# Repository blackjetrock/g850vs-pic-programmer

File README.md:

# g850vs-pic-programmer
PIC programmer for G850VS

These are the files for a PIC programmer for a Sharp PC-G850V or PC-G850VS pocket computer.
The PIC programmer is from a ciruit i found on the internet. I have had permission to use the circuit
so that people can use it to program PICs. 

The PIC prototype PCB is based on the test circuit in the PC-G850 manual, except that, for some reaosn,
I changed the GPIO line that the LED is driven from. The example program given in the manual will have to 
be adjusted appropriately.

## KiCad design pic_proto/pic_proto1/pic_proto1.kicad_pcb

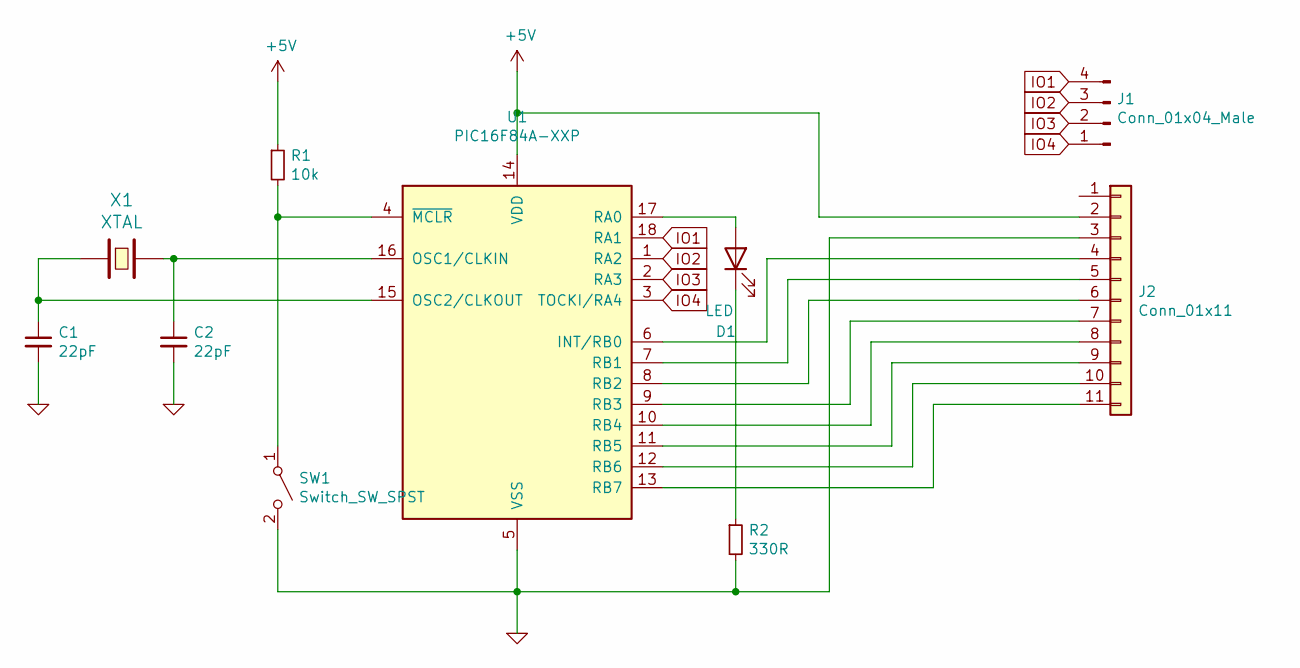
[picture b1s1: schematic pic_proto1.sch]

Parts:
C1, C2: 22pF; C_Disc_D7.5mm_W5.0mm_P5.00mm
D1: LED; LED_D5.0mm
J1: Conn_01x04_Male; Molex_KK-254_AE-6410-04A_1x04_P2.54mm_Vertical
J2: Conn_01x11; Molex_KK-254_AE-6410-11A_1x11_P2.54mm_Vertical
R1: 10k; R_Axial_DIN0204_L3.6mm_D1.6mm_P7.62mm_Horizontal
R2: 330R; R_Axial_DIN0204_L3.6mm_D1.6mm_P7.62mm_Horizontal
SW1: Switch_SW_SPST; SW_PUSH-12mm
U1: PIC16F84A-XXP; DIP-18_W7.62mm
X1: XTAL; Crystal_HC49-4H_Vertical

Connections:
+5V: J2.2, R1.1, U1.14 (VDD)
GND: C1.2, C2.2, J2.3, R2.2, SW1.2 (B), U1.5 (VSS)
IO1: J1.4, U1.18 (RA1)
IO2: J1.3, U1.1 (RA2)
IO3: J1.2, U1.2 (RA3)
IO4: J1.1, U1.3 (TOCKI/RA4)
unnamed: C1.1, U1.15 (OSC2/CLKOUT), X1.1
unnamed: C2.1, U1.16 (OSC1/CLKIN), X1.2
unnamed: D1.1 (K), R2.1
unnamed: D1.2 (A), U1.17 (RA0)
unnamed: J2.4, U1.6 (INT/RB0)
unnamed: J2.5, U1.7 (RB1)
unnamed: J2.6, U1.8 (RB2)
unnamed: J2.7, U1.9 (RB3)
unnamed: J2.8, U1.10 (RB4)
unnamed: J2.9, U1.11 (RB5)
unnamed: J2.10, U1.12 (RB6)
unnamed: J2.11, U1.13 (RB7)
unnamed: R1.2, SW1.1 (A), U1.4 (~MCLR~)

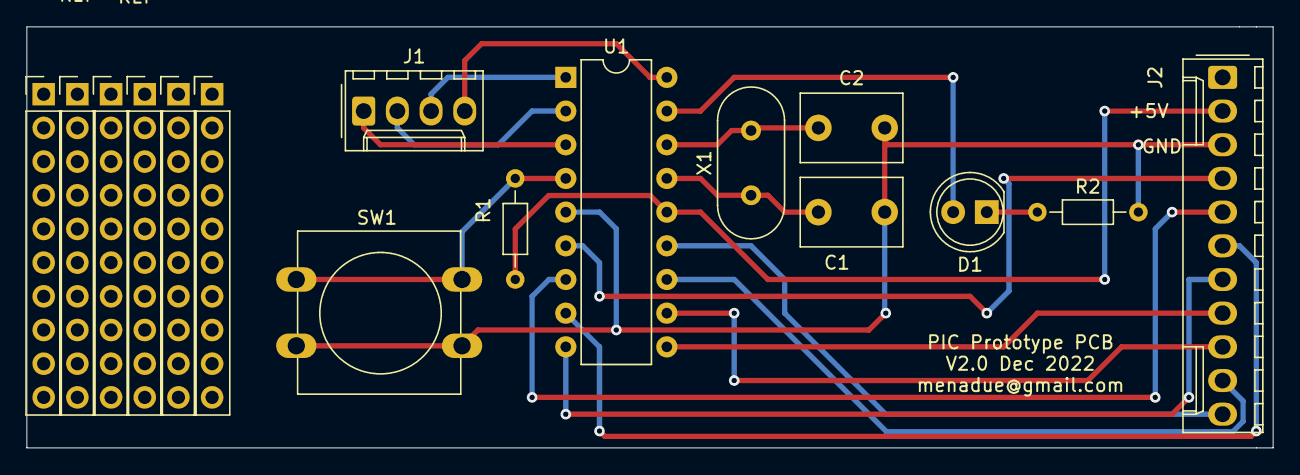
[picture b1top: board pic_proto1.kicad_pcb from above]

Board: 2 copper layers, 94.0 x 31.8 mm, 10 parts (0 on the bottom side), 19 nets.

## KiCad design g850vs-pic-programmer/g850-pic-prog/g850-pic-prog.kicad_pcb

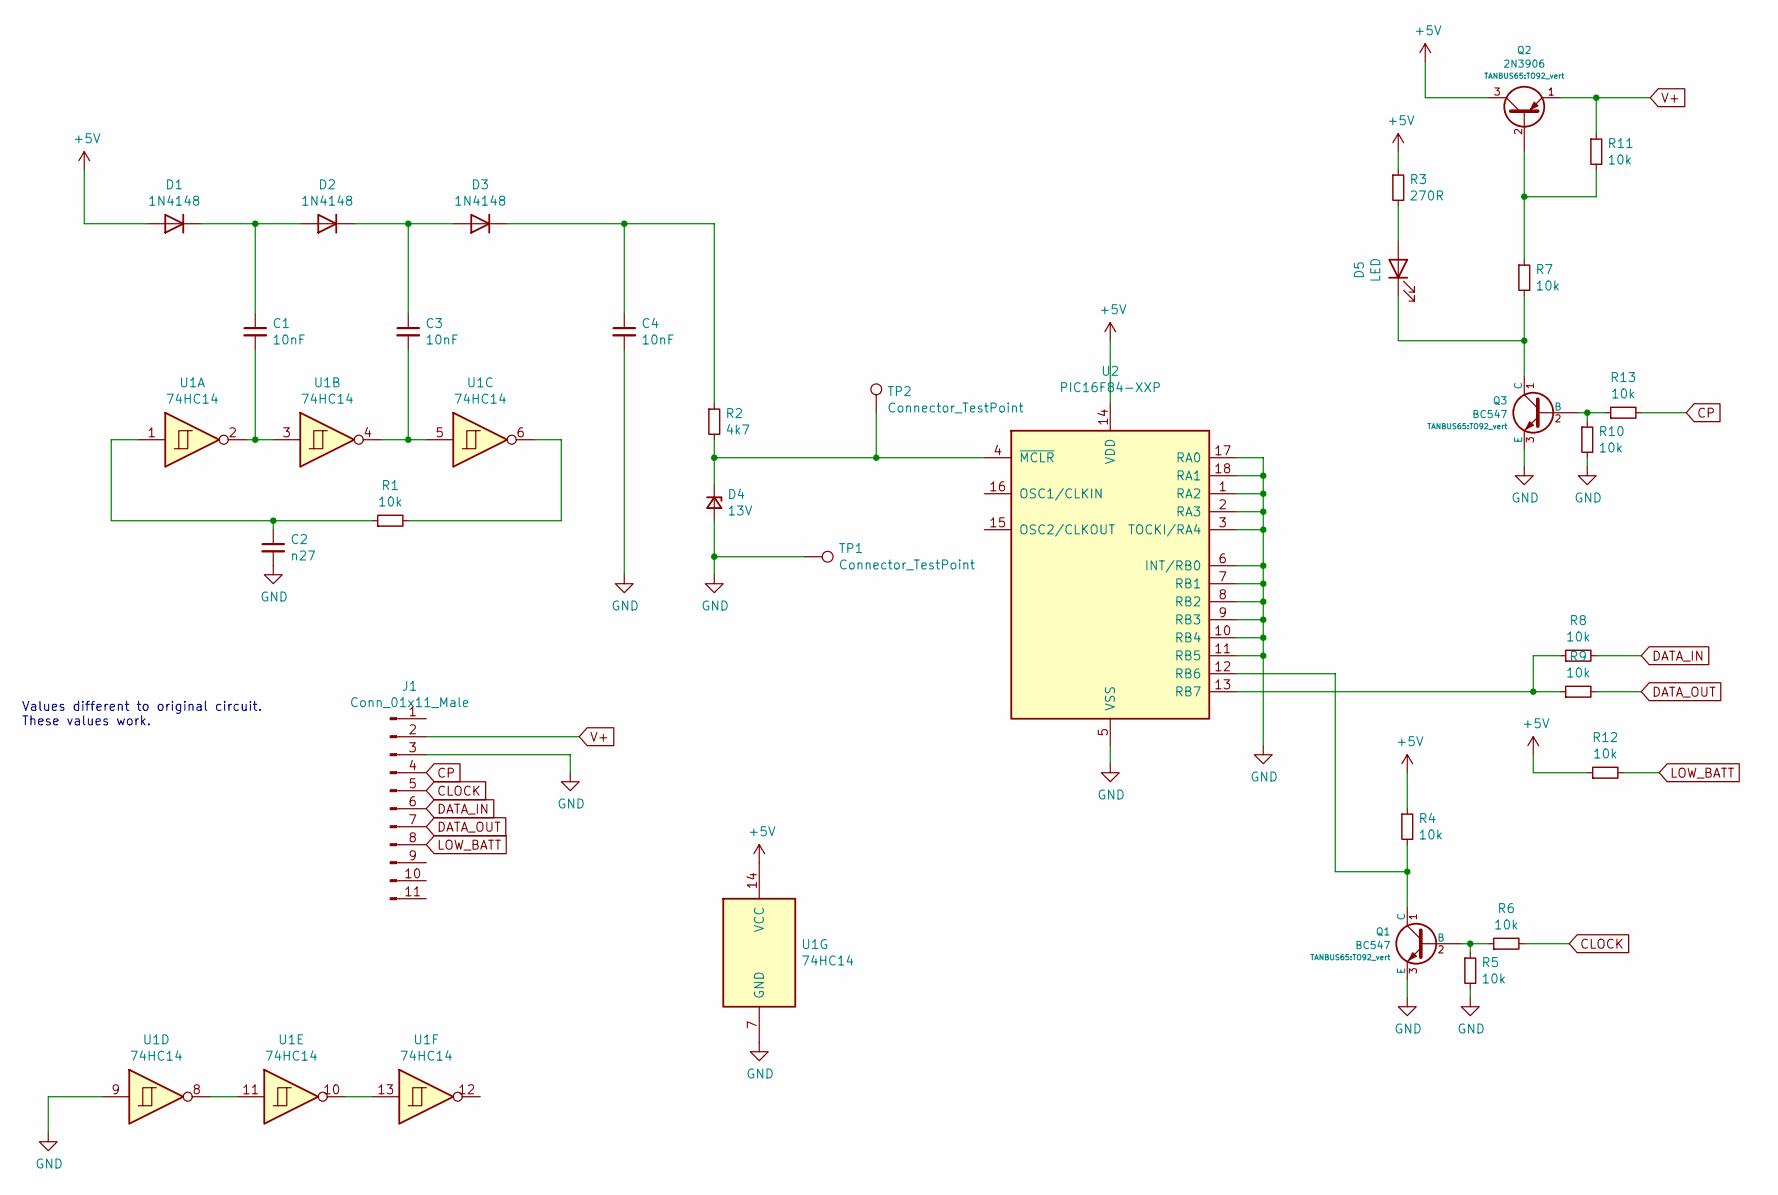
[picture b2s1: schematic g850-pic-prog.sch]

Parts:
C1, C3, C4: 10nF; C_Axial_L5.1mm_D3.1mm_P7.50mm_Horizontal
C2: n27; C_Axial_L5.1mm_D3.1mm_P7.50mm_Horizontal
D1, D2, D3: 1N4148; D_DO-35_SOD27_P7.62mm_Horizontal
D4: 13V; D_DO-35_SOD27_P7.62mm_Horizontal
D5: LED; LED_D5.0mm
J1: Conn_01x11_Male; Molex_KK-254_AE-6410-11A_1x11_P2.54mm_Vertical
Q1, Q3: BC547; TO92_vert
Q2: 2N3906; TO92_vert
R1, R4, R5, R6, R7, R8, R9, R10, R11, R12, R13: 10k; R_Axial_DIN0207_L6.3mm_D2.5mm_P7.62mm_Horizontal
R2: 4k7; R_Axial_DIN0207_L6.3mm_D2.5mm_P7.62mm_Horizontal
R3: 270R; R_Axial_DIN0207_L6.3mm_D2.5mm_P7.62mm_Horizontal
TP1, TP2: Connector_TestPoint; TestPoint_Loop_D1.80mm_Drill1.0mm_Beaded
U1: 74HC14; DIP-14_W7.62mm
U2: PIC16F84-XXP; DIP_Socket-18_W4.3_W5.08_W7.62_W10.16_W10.9_3M_218-3341-00-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

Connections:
+5V: D1.2 (A), Q2.3 (C), R3.1, R4.1, R12.1, U1.14 (VCC), U2.14 (VDD)
CLOCK: J1.5, R6.2
CP: J1.4, R13.2
DATA_IN: J1.6, R8.2
DATA_OUT: J1.7, R9.2
GND: C2.2, C4.2, D4.2 (A), J1.3, Q1.3 (E), Q3.3 (E), R5.2, R10.2, TP1.1, U1.7 (GND), U1.9, U2.1 (RA2), U2.2 (RA3), U2.3 (TOCKI/RA4), U2.5 (VSS), U2.6 (INT/RB0), U2.7 (RB1), U2.8 (RB2), U2.9 (RB3), U2.10 (RB4), U2.11 (RB5), U2.17 (RA0), U2.18 (RA1)
LOW_BATT: J1.8, R12.2
unnamed: C1.1, D1.1 (K), D2.2 (A)
unnamed: C1.2, U1.2, U1.3
unnamed: C2.1, R1.1, U1.1
unnamed: C3.1, D2.1 (K), D3.2 (A)
unnamed: C3.2, U1.4, U1.5
unnamed: C4.1, D3.1 (K), R2.1
unnamed: D4.1 (K), R2.2, TP2.1, U2.4 (~MCLR~)
unnamed: D5.1 (K), Q3.1 (C), R7.2
unnamed: D5.2 (A), R3.2
unnamed: Q1.1 (C), R4.2, U2.12 (RB6)
unnamed: Q1.2 (B), R5.1, R6.1
unnamed: Q2.2 (B), R7.1, R11.2
unnamed: Q3.2 (B), R10.1, R13.1
unnamed: R1.2, U1.6
unnamed: R8.1, R9.1, U2.13 (RB7)
unnamed: U1.10, U1.13
unnamed: U1.8, U1.11
V+: J1.2, Q2.1 (E), R11.1

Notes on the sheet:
Values different to original circuit. These values work.

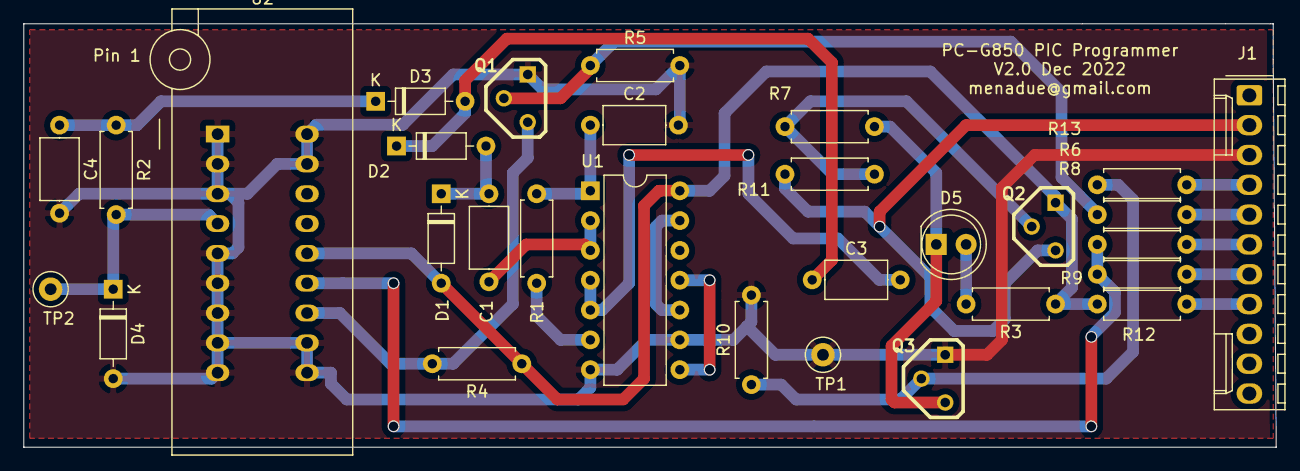
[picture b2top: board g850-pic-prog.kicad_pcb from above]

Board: 2 copper layers, 106.7 x 36.1 mm, 30 parts (0 on the bottom side), 25 nets.

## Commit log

2021-01-13 Added PIC programmer and PIC prototype PCB files.
2021-02-07 Updated values on PIC programmer to get one of my PCBs working. Capacitor values don't seem to be correct on original circuit.
2021-02-07 C2 should be n27, or 270pF. 10nF does not work.
